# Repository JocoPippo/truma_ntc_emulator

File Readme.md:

## TRUMA NTC EMU
Questo progetto è nato per risolvere il problema dell'instabilità della regolazione della stufa truma.
In rete si trovano altri progetti che si basano sulla regolazione di tipo on/off con i sistemi più disparati, 
putroppo questo tipo di regolazioni mal si abbina alla stufa poichè non consente di sfruttare la regolazione della
velocità e della portata del riscaldatore.
Ho cercato di superare questo problema utilizzando un potenziometro digitale abbinato ad un microcontrollore STM32f103.
Nel folder HW è presente lo schema elettrico e il pcb in formato kicad.

Nel folder cubePrj è presente l'export da Stm32CubeIde del progetto. 
Attualmente sono stati sviluppati due portotipi che sono installati per il test.

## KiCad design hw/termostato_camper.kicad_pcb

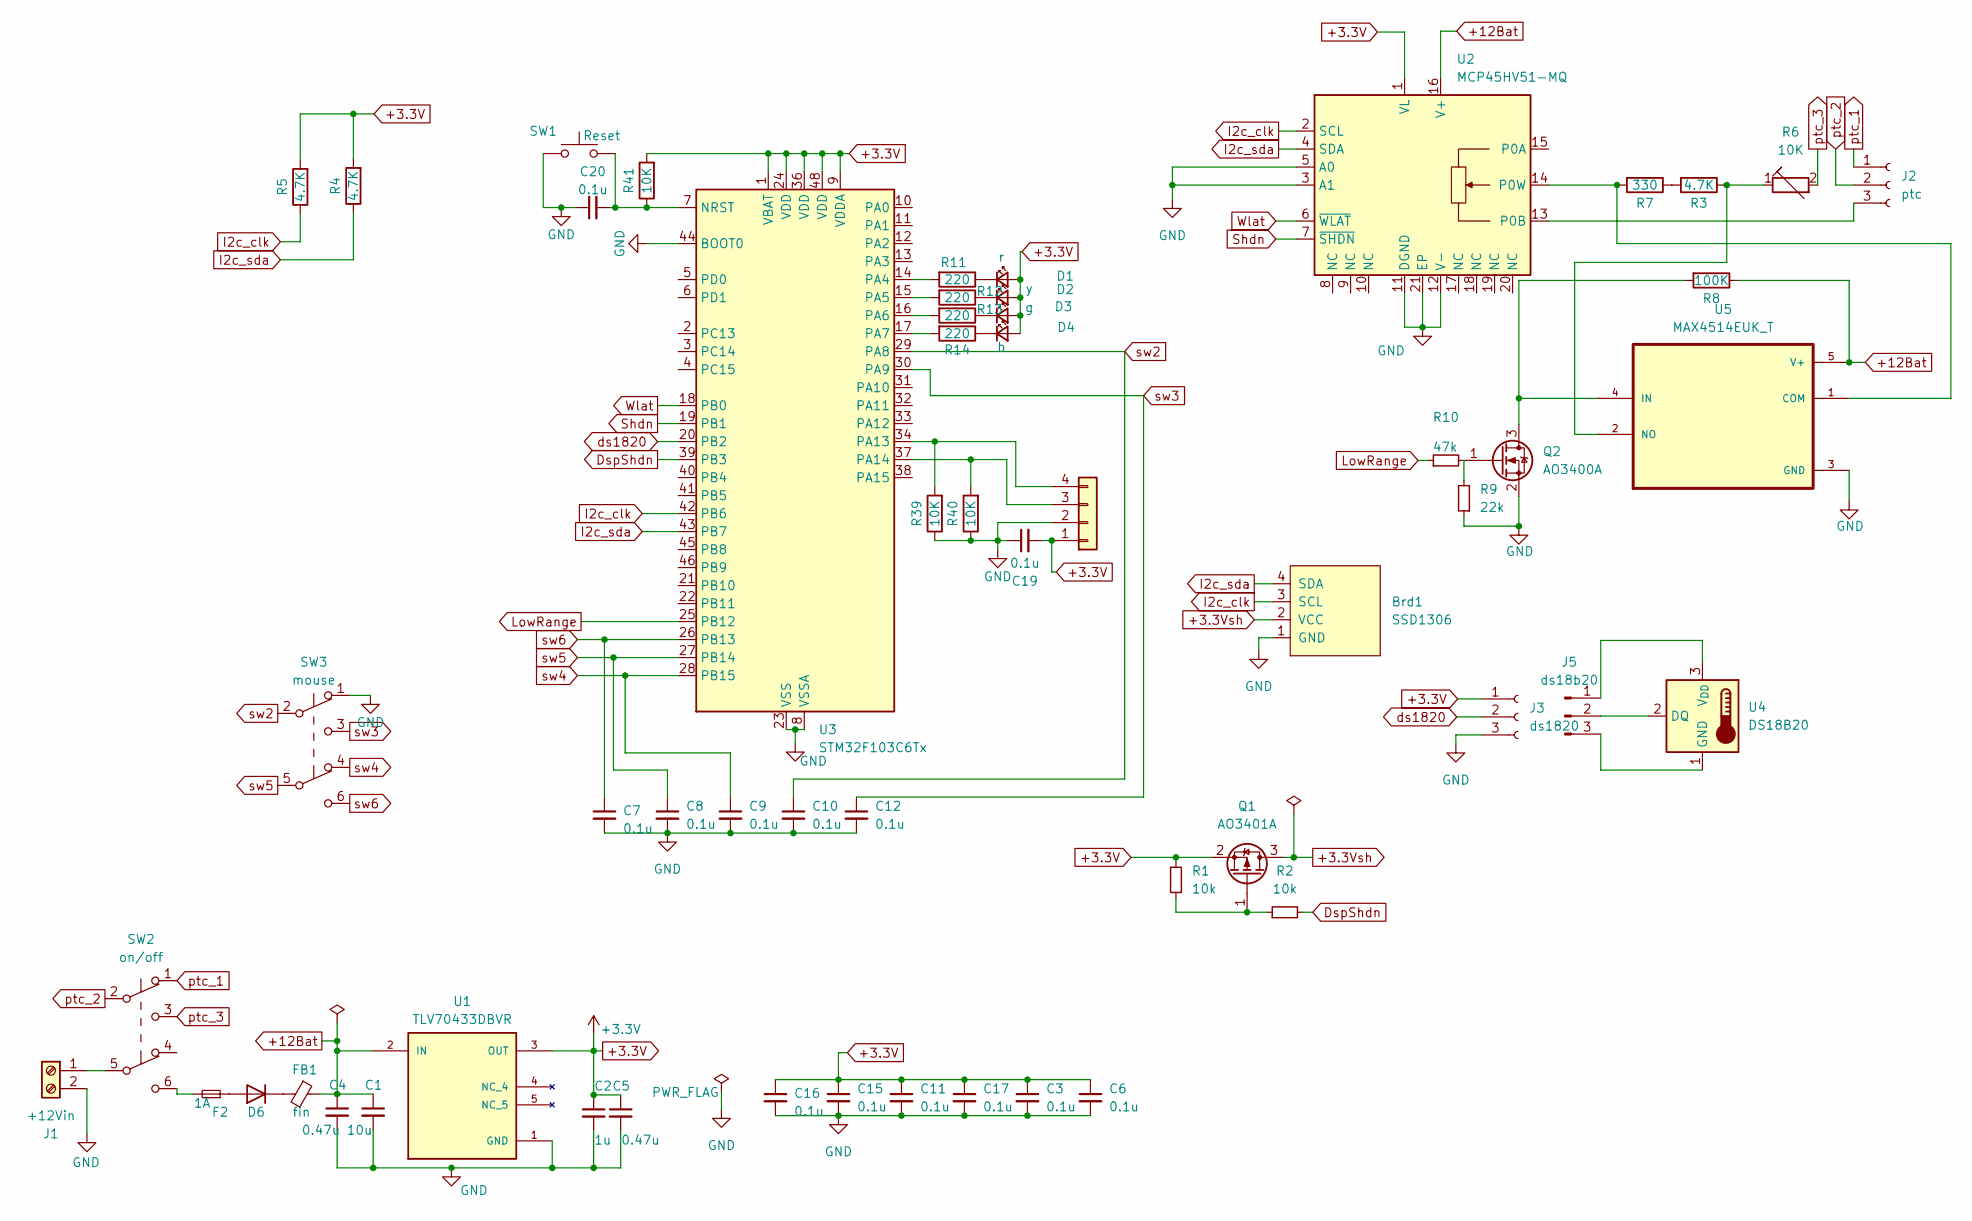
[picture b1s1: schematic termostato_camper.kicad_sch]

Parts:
Brd1: SSD1306; 128x64OLED
C1: 10u; CP_EIA-7343-15_Kemet-W
C2: 1u; C_1206_3216Metric_Pad1.33x1.80mm_HandSolder
C3, C6, C7, C8, C9, C10, C11, C12, C15, C16, C17, C19, C20: 0.1u; C_0805_2012Metric
C4, C5: 0.47u; C_0805_2012Metric_Pad1.18x1.45mm_HandSolder
D1: r; D_0805_2012Metric
D2: y; D_0805_2012Metric
D3: g; D_0805_2012Metric
D4: b; D_0805_2012Metric
D6: SS14; D_SOD-123
F2: 1A; Fuse_1206_3216Metric
FB1: fin; L_0805_2012Metric
J1: +12Vin; TerminalBlock_Phoenix_MKDS-1,5-2-5.08_1x02_P5.08mm_Horizont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
J2: ptc; JST_XA_B03B-XASK-1_1x03_P2.50mm_Vertical
J3: ds1820; JST_XA_B03B-XASK-1_1x03_P2.50mm_Vertical
J4: Jtag; PinSocket_1x04_P1.27mm_Vertical
J5: ds18b20
Q1: AO3401A; SOT-23
Q2: AO3400A; SOT-23
R1, R2: 10k; R_0805_2012Metric
R3, R4, R5: 4.7K; R_0805_2012Metric_Pad1.20x1.40mm_HandSolder
R6: 10K; Potentiometer_Bourns_3266Y_Vertical
R7: 330; R_0805_2012Metric_Pad1.20x1.40mm_HandSolder
R8: 100K; R_0805_2012Metric_Pad1.20x1.40mm_HandSolder
R9: 22k; R_0805_2012Metric
R10: 47k; R_0805_2012Metric
R11, R12, R13, R14: 220; R_0805_2012Metric_Pad1.20x1.40mm_HandSolder
R39, R40, R41: 10K; R_0805_2012Metric_Pad1.20x1.40mm_HandSolder
SW1: Reset; SW_Tactile_SPST_NO_Straight_CK_PTS636Sx25SMTRLFS
SW2: on/off; switch_dpdt
SW3: mouse; tactile_5
U1: TLV70433DBVR; SOT-23-5; PARTREV D
U2: MCP45HV51-MQ; QFN-20-1EP_5x5mm_P0.65mm_EP3.35x3.35mm
U3: STM32F103C6Tx; LQFP-48_7x7mm_P0.5mm
U4: DS18B20
U5: MAX4514EUK_T; SOT95P280X145-5N

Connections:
+3.3V: C2.1, C3.1, C5.1, C6.1, C11.1, C15.1, C16.1, C17.1, C19.2, D1.2 (A), D2.2 (A), D3.2 (A), D4.2 (A), J3.1, J4.1, Q1.2 (S), R1.2, R4.2, R5.2, R41.2, U1.3 (OUT), U2.1 (VL), U3.1 (VBAT), U3.9 (VDDA), U3.24 (VDD), U3.36 (VDD), U3.48 (VDD)
+3.3Vsh: Brd1.2 (VCC), Q1.3 (D)
+12Bat: C1.1, C4.1, FB1.1, R8.1, U1.2 (IN), U2.16 (V+), U5.5 (V+)
DspShdn: R2.2, U3.39 (PB3)
GND: Brd1.1 (GND), C1.2, C2.2, C3.2, C4.2, C5.2, C6.2, C7.2, C8.2, C9.2, C10.2, C11.2, C12.2, C15.2, C16.2, C17.2, C19.1, C20.1, J1.2, J3.3, J4.2, Q2.2 (S), R9.1, R39.1, R40.1, SW1.1, SW3.1 (A), U1.1 (GND), U1.4 (NC_4), U1.5 (NC_5), U2.3 (A1), U2.5 (A0), U2.11 (DGND), U2.12 (V-), U2.21 (EP), U3.8 (VSSA), U3.23 (VSS), U3.35 (VSS), U3.44 (BOOT0), U3.47 (VSS), U5.3 (GND)
I2c_clk: Brd1.3 (SCL), R5.1, U2.2 (SCL), U3.42 (PB6)
I2c_sda: Brd1.4 (SDA), R4.1, U2.4 (SDA), U3.43 (PB7)
LowRange: R10.1, U3.25 (PB12)
unnamed: D1.1 (K), R11.1
unnamed: D2.1 (K), R12.1
unnamed: D3.1 (K), R13.1
unnamed: D4.1 (K), R14.1
unnamed: D6.2 (A), F2.1
unnamed: D6.1 (K), FB1.2
unnamed: F2.2, SW2.6 (C)
unnamed: J1.1, SW2.5 (B)
unnamed: J2.3, U2.13 (P0B)
unnamed: J4.3, R40.2, U3.37 (PA14)
unnamed: J4.4, R39.2, U3.34 (PA13)
unnamed: J5.1, U4.3 (V_{DD})
unnamed: J5.2, U4.2 (DQ)
unnamed: J5.3, U4.1 (GND)
unnamed: Q1.1 (G), R1.1, R2.1
unnamed: Q2.3 (D), R8.2, U5.4 (IN)
unnamed: Q2.1 (G), R9.2, R10.2
unnamed: R3.2, R7.1
unnamed: R7.2, U2.14 (P0W), U5.1 (COM)
unnamed: C20.2, R41.1, SW1.2, U3.7 (NRST)
unnamed: R11.2, U3.14 (PA4)
unnamed: R12.2, U3.15 (PA5)
unnamed: R13.2, U3.16 (PA6)
unnamed: R14.2, U3.17 (PA7)
unnamed: R3.1, R6.1, U5.2 (NO)
Shdn: U2.7 (~SHDN), U3.19 (PB1)
Wlat: U2.6 (~WLAT), U3.18 (PB0)
ds1820: J3.2, U3.20 (PB2)
ptc_1: J2.1, SW2.1 (A)
ptc_2: J2.2, SW2.2 (B)
ptc_3: R6.2, SW2.3 (C)
sw2: C10.1, SW3.2 (B), U3.29 (PA8)
sw3: C12.1, SW3.3 (C), U3.30 (PA9)
sw4: C9.1, SW3.4 (A), U3.28 (PB15)
sw5: C8.1, SW3.5 (B), U3.27 (PB14)
sw6: C7.1, SW3.6 (C), U3.26 (PB13)

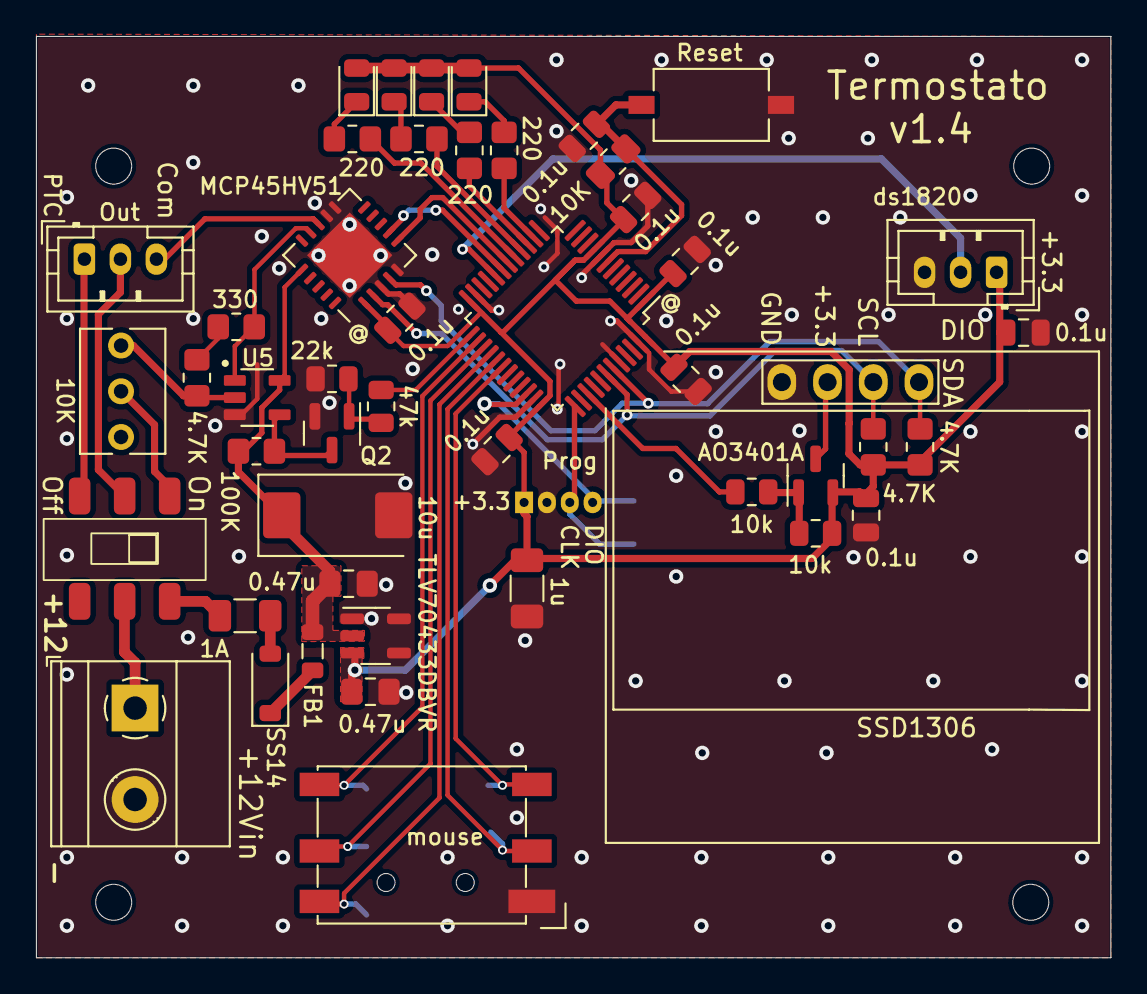
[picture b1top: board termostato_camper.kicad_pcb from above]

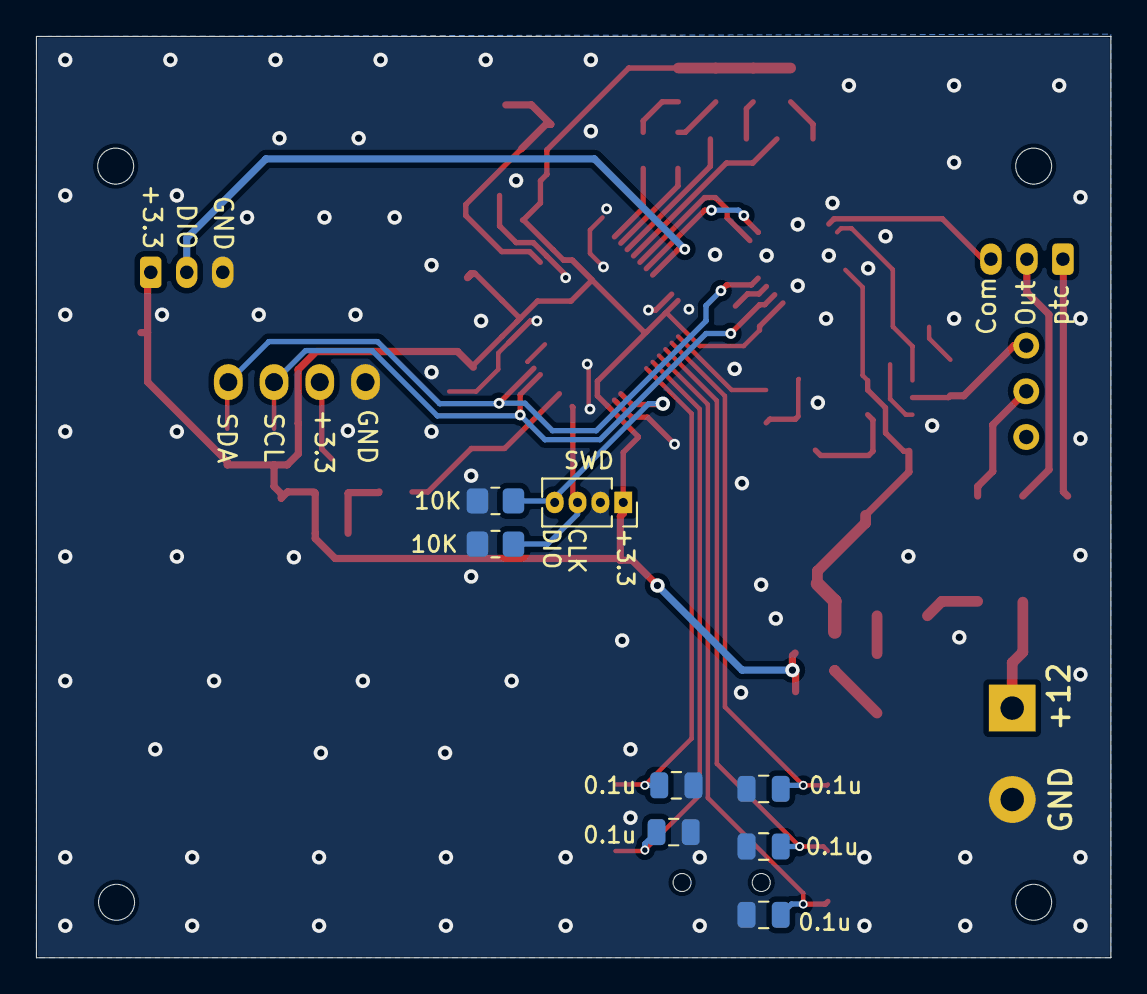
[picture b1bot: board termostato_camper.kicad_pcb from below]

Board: 2 copper layers, 59.7 x 51.2 mm, 55 parts (8 on the bottom side), 41 nets.

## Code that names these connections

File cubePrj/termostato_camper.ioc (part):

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Mcu.Name=STM32F103C(4-6)Tx
Mcu.Package=LQFP48
Mcu.UserName=STM32F103C6Tx
PA13.Mode=Serial_Wire
PA13.Signal=SYS_JTMS-SWDIO
PA14.Mode=Serial_Wire
PA14.Signal=SYS_JTCK-SWCLK
PA4.GPIOParameters=PinState,GPIO_Label
PA4.GPIO_Label=DL_RED
PA4.PinState=GPIO_PIN_SET
PA4.Signal=GPIO_Output
PA5.GPIOParameters=PinState,GPIO_Label
PA5.GPIO_Label=DL_YELLOW
PA5.PinState=GPIO_PIN_SET
PA5.Signal=GPIO_Output
PA6.GPIOParameters=PinState,GPIO_Label
PA6.GPIO_Label=DL_GREEN
PA6.PinState=GPIO_PIN_SET
PA6.Signal=GPIO_Output
PA7.GPIOParameters=PinState,GPIO_Label
PA7.GPIO_Label=DL_BLUE
PA7.PinState=GPIO_PIN_SET
PA7.Signal=GPIO_Output
PA8.GPIOParameters=GPIO_PuPd,GPIO_Label,GPIO_ModeDefaultEXTI
PA8.GPIO_Label=SW_DX
PA8.GPIO_ModeDefaultEXTI=GPIO_MODE_IT_RISING_FALLING
PA8.GPIO_PuPd=GPIO_PULLUP
PA8.Signal=GPXTI8
PA9.GPIOParameters=GPIO_PuPd,GPIO_Label,GPIO_ModeDefaultEXTI
PA9.GPIO_Label=SW_ENTER
PA9.GPIO_ModeDefaultEXTI=GPIO_MODE_IT_RISING_FALLING
PA9.GPIO_PuPd=GPIO_PULLUP
PA9.Signal=GPXTI9
PB0.GPIOParameters=GPIO_Label
PB0.GPIO_Label=Wlat
PB0.Signal=GPIO_Output
PB1.GPIOParameters=PinState,GPIO_Label
PB1.GPIO_Label=Shdn
PB1.PinState=GPIO_PIN_SET
PB1.Signal=GPIO_Output
PB12.GPIOParameters=GPIO_Label
PB12.GPIO_Label=LowRange
PB12.Signal=GPIO_Output
PB13.GPIOParameters=GPIO_PuPd,GPIO_Label,GPIO_ModeDefaultEXTI
PB13.GPIO_Label=SW_SU
PB13.GPIO_ModeDefaultEXTI=GPIO_MODE_IT_RISING_FALLING
PB13.GPIO_PuPd=GPIO_PULLUP
PB13.Signal=GPXTI13
PB14.GPIOParameters=GPIO_PuPd,GPIO_Label,GPIO_ModeDefaultEXTI
PB14.GPIO_Label=SW_SX
PB14.GPIO_ModeDefaultEXTI=GPIO_MODE_IT_RISING_FALLING
PB14.GPIO_PuPd=GPIO_PULLUP
PB14.Signal=GPXTI14
PB15.GPIOParameters=GPIO_PuPd,GPIO_Label,GPIO_ModeDefaultEXTI
PB15.GPIO_Label=SW_GIU
PB15.GPIO_ModeDefaultEXTI=GPIO_MODE_IT_RISING_FALLING
PB15.GPIO_PuPd=GPIO_PULLUP
PB15.Signal=GPXTI15
PB2.GPIOParameters=GPIO_Label
PB2.GPIO_Label=DS1820_IO
PB2.Signal=GPIO_Input
PB3.GPIOParameters=GPIO_Label
PB3.GPIO_Label=LCD_Shdn
PB3.Signal=GPIO_Output
PB6.Mode=I2C
PB6.Signal=I2C1_SCL
PB7.Mode=I2C
PB7.Signal=I2C1_SDA
RCC.SYSCLKFreq_VALUE=8000000
board=custom

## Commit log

2024-05-30 Add files via upload
    First issue
2024-06-02 Update Readme.txt
    add picture
